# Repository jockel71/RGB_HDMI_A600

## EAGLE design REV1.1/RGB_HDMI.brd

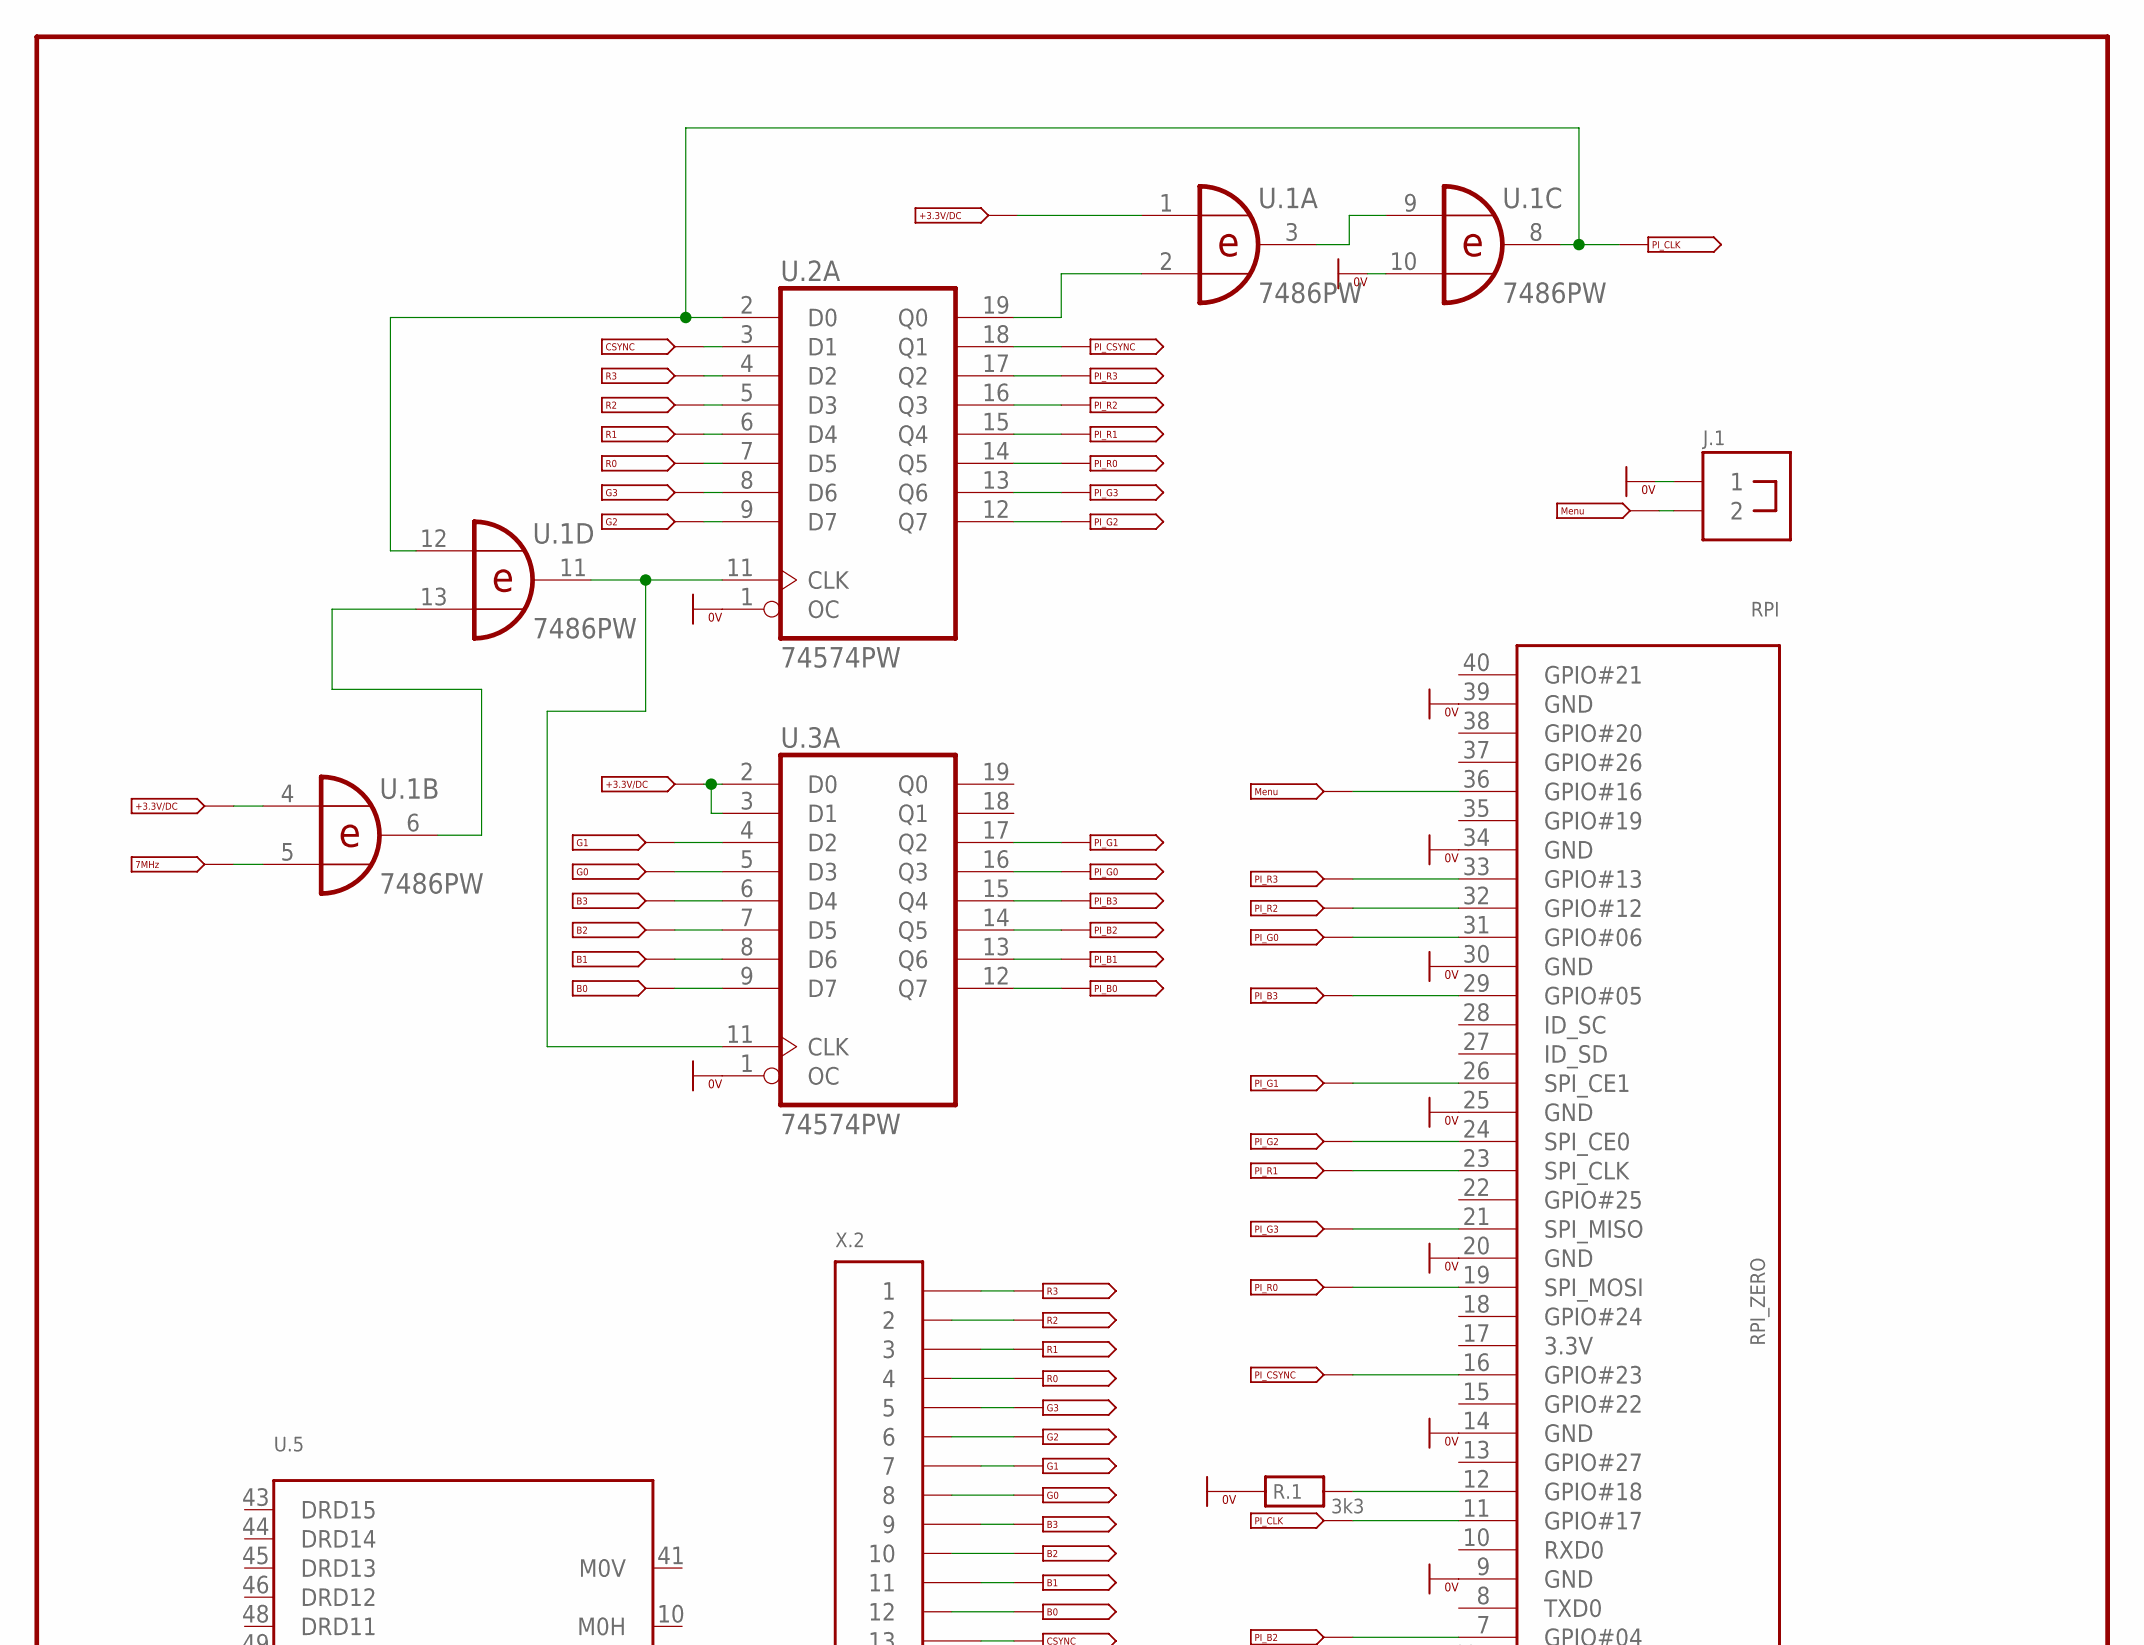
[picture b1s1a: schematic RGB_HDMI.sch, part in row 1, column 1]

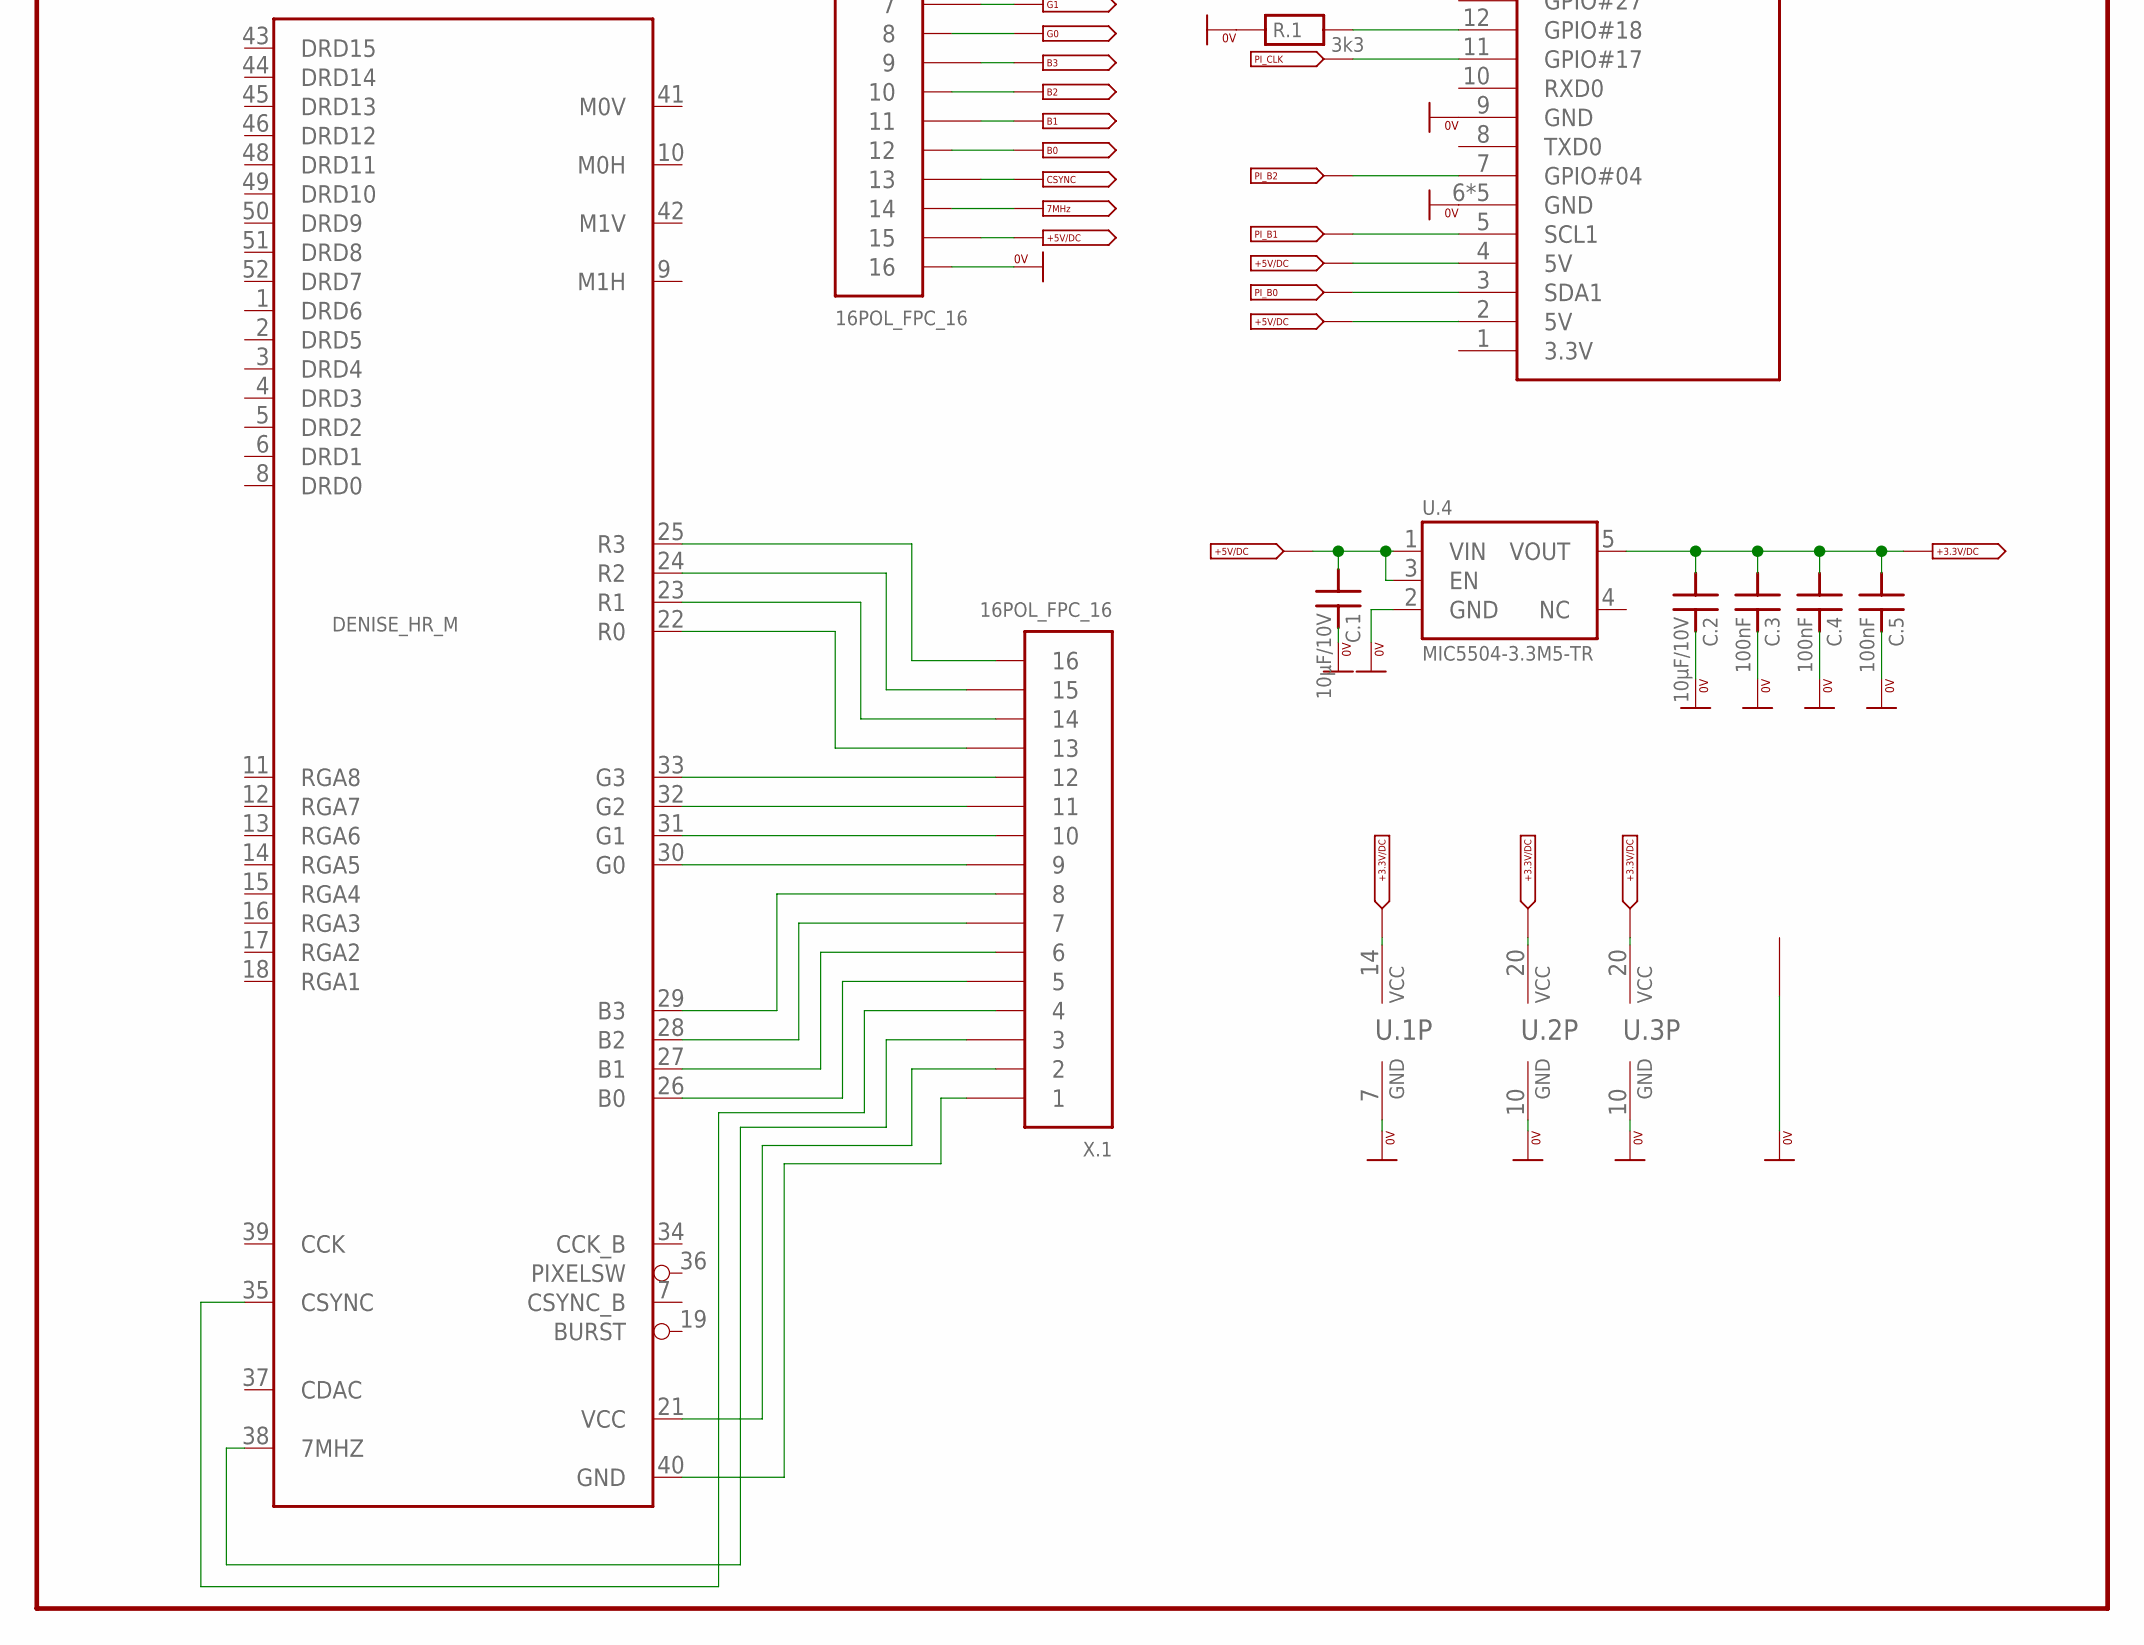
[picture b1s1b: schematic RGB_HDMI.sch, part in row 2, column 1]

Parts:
C.1, C.2: 10µF/10V; 0805
C.3, C.4, C.5: 100nF; 0805
J.1: 2POLIG_1REIHIG
K.1: PAD_1,0SQ; 1,0SQ
R.1: 3k3; 0805
RPI: RPI_ZERO; RPI_ZERO_FULL
U.1: 7486PW; TSSOP14
U.2, U.3: 74574PW; TSSOP20
U.4: MIC5504-3.3M5-TR; SOT23-5
U.5: DENISE_HR_M; PLCC_52_MIRROR
X.1, X.2: 16POL_FPC_16; MOLEX_FPC_16

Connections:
0V: C.1.2, C.2.2, C.3.2, C.4.2, C.5.2, J.1.1, K.1.P$1, R.1.1, RPI.6 (GND), RPI.9 (GND), RPI.14 (GND), RPI.20 (GND), RPI.25 (GND), RPI.30 (GND), RPI.34 (GND), RPI.39 (GND), RPI.P$1 (GND), RPI.P$2 (GND), RPI.P$3 (GND), RPI.P$4 (GND), U.1.7 (GND), U.1.10 (I1), U.2.1 (OC), U.2.10 (GND), U.3.1 (OC), U.3.10 (GND), U.4.2 (GND), X.2.16
7MHZ: U.1.5 (I1), X.2.14
+3.3V: C.2.1, C.3.1, C.4.1, C.5.1, U.1.1 (I0), U.1.4 (I0), U.1.14 (VCC), U.2.20 (VCC), U.3.2 (D0), U.3.3 (D1), U.3.20 (VCC), U.4.5 (VOUT)
+5V: C.1.1, RPI.2 (5V), RPI.4 (5V), U.4.1 (VIN), U.4.3 (EN), X.2.15
B0: U.3.9 (D7), X.2.12
B1: U.3.8 (D6), X.2.11
B2: U.3.7 (D5), X.2.10
B3: U.3.6 (D4), X.2.9
CSYNC: U.2.3 (D1), X.2.13
G0: U.3.5 (D3), X.2.8
G1: U.3.4 (D2), X.2.7
G2: U.2.9 (D7), X.2.6
G3: U.2.8 (D6), X.2.5
GND: U.5.40 (GND), X.1.1
MENUE: J.1.2, RPI.36 (GPIO#16)
unnamed: U.1.6 (O), U.1.13 (I1)
unnamed: U.5.25 (R3), X.1.16
unnamed: U.5.24 (R2), X.1.15
unnamed: U.5.23 (R1), X.1.14
unnamed: U.5.22 (R0), X.1.13
unnamed: U.1.11 (O), U.2.11 (CLK), U.3.11 (CLK)
unnamed: U.1.2 (I1), U.2.19 (Q0)
unnamed: U.1.3 (O), U.1.9 (I0)
unnamed: U.5.30 (G0), X.1.9
unnamed: U.5.31 (G1), X.1.10
unnamed: U.5.32 (G2), X.1.11
unnamed: U.5.33 (G3), X.1.12
unnamed: U.5.29 (B3), X.1.8
unnamed: U.5.28 (B2), X.1.7
unnamed: U.5.27 (B1), X.1.6
unnamed: U.5.26 (B0), X.1.5
unnamed: U.5.21 (VCC), X.1.2
unnamed: U.5.38 (7MHZ), X.1.3
unnamed: U.5.35 (CSYNC), X.1.4
unnamed: R.1.2, RPI.12 (GPIO#18)
PI_B0: RPI.3 (SDA1), U.3.12 (Q7)
PI_B1: RPI.5 (SCL1), U.3.13 (Q6)
PI_B2: RPI.7 (GPIO#04), U.3.14 (Q5)
PI_B3: RPI.29 (GPIO#05), U.3.15 (Q4)
PI_CLK: RPI.11 (GPIO#17), U.1.8 (O), U.1.12 (I0), U.2.2 (D0)
PI_CSYNC: RPI.16 (GPIO#23), U.2.18 (Q1)
PI_G0: RPI.31 (GPIO#06), U.3.16 (Q3)
PI_G1: RPI.26 (SPI_CE1), U.3.17 (Q2)
PI_G2: RPI.24 (SPI_CE0), U.2.12 (Q7)
PI_G3: RPI.21 (SPI_MISO), U.2.13 (Q6)
PI_R0: RPI.19 (SPI_MOSI), U.2.14 (Q5)
PI_R1: RPI.23 (SPI_CLK), U.2.15 (Q4)
PI_R2: RPI.32 (GPIO#12), U.2.16 (Q3)
PI_R3: RPI.33 (GPIO#13), U.2.17 (Q2)
R0: U.2.7 (D5), X.2.4
R1: U.2.6 (D4), X.2.3
R2: U.2.5 (D3), X.2.2
R3: U.2.4 (D2), X.2.1

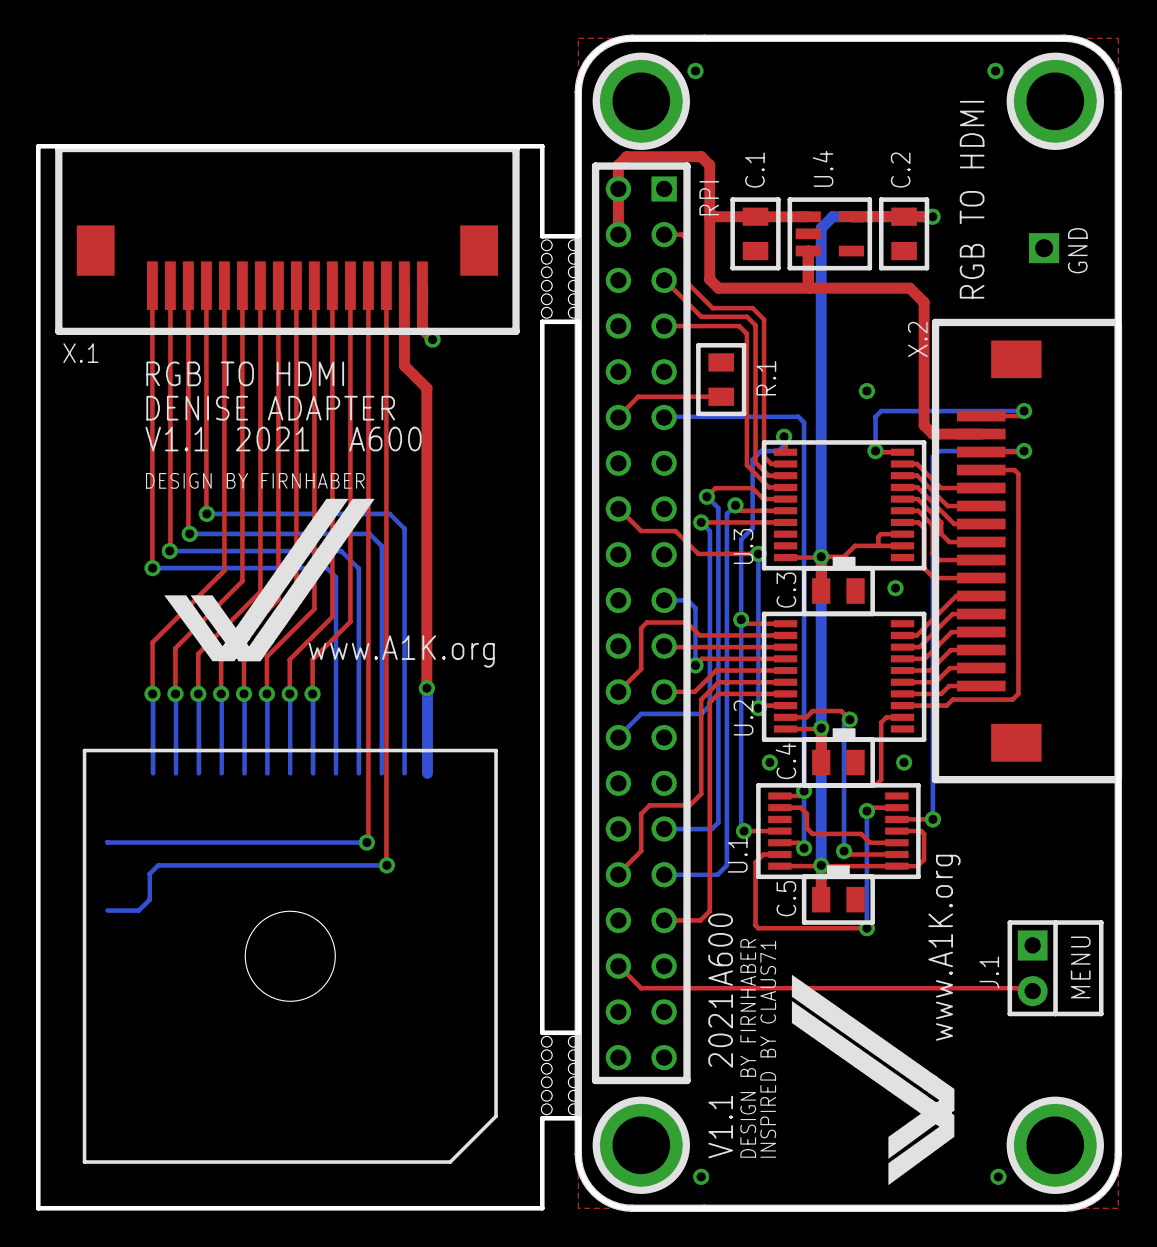
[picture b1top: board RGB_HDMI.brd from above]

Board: 2 copper layers, 60.0 x 65.0 mm, 16 parts (1 on the bottom side), 53 nets.
